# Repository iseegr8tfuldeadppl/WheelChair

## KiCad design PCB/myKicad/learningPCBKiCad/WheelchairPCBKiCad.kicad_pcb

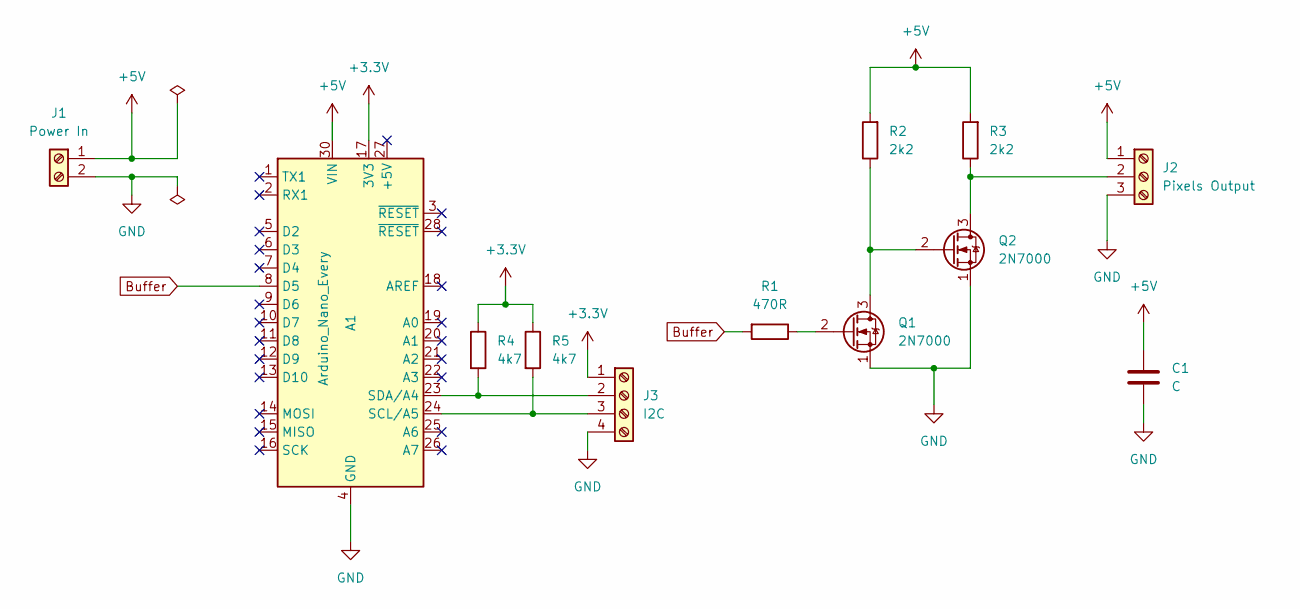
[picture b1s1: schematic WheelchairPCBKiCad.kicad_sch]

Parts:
A1: Arduino_Nano_Every; Arduino_Nano
C1: C; C_Radial_D10.0mm_H20.0mm_P5.00mm
J1: Power In; TerminalBlock_Phoenix_MKDS-3-2-5.08_1x02_P5.08mm_Horizontal
J2: Pixels Output; TerminalBlock_Phoenix_MKDS-1,5-3_1x03_P5.00mm_Horizontal
J3: I2C; TerminalBlock_Phoenix_PT-1,5-4-5.0-H_1x04_P5.00mm_Horizontal
Q1, Q2: 2N7000; TO-92L_HandSolder
R1: 470R; R_Axial_DIN0207_L6.3mm_D2.5mm_P10.16mm_Horizontal
R2, R3: 2k2; R_Axial_DIN0207_L6.3mm_D2.5mm_P10.16mm_Horizontal
R4, R5: 4k7; R_Axial_DIN0207_L6.3mm_D2.5mm_P10.16mm_Horizontal

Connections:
+3V3: A1.17 (3V3), J3.1, R4.1, R5.1
+5V: A1.30 (VIN), C1.1, J1.1, J2.1, R2.2, R3.2
Buffer: A1.8 (D5), R1.2
GND: A1.4 (GND), A1.29 (GND), C1.2, J1.2, J2.3, J3.4, Q1.1 (S), Q2.1 (S)
unnamed: A1.23 (SDA/A4), J3.2, R4.2
unnamed: A1.24 (SCL/A5), J3.3, R5.2
unnamed: Q1.2 (G), R1.1
unnamed: Q1.3 (D), Q2.2 (G), R2.1
unnamed: J2.2, Q2.3 (D), R3.1

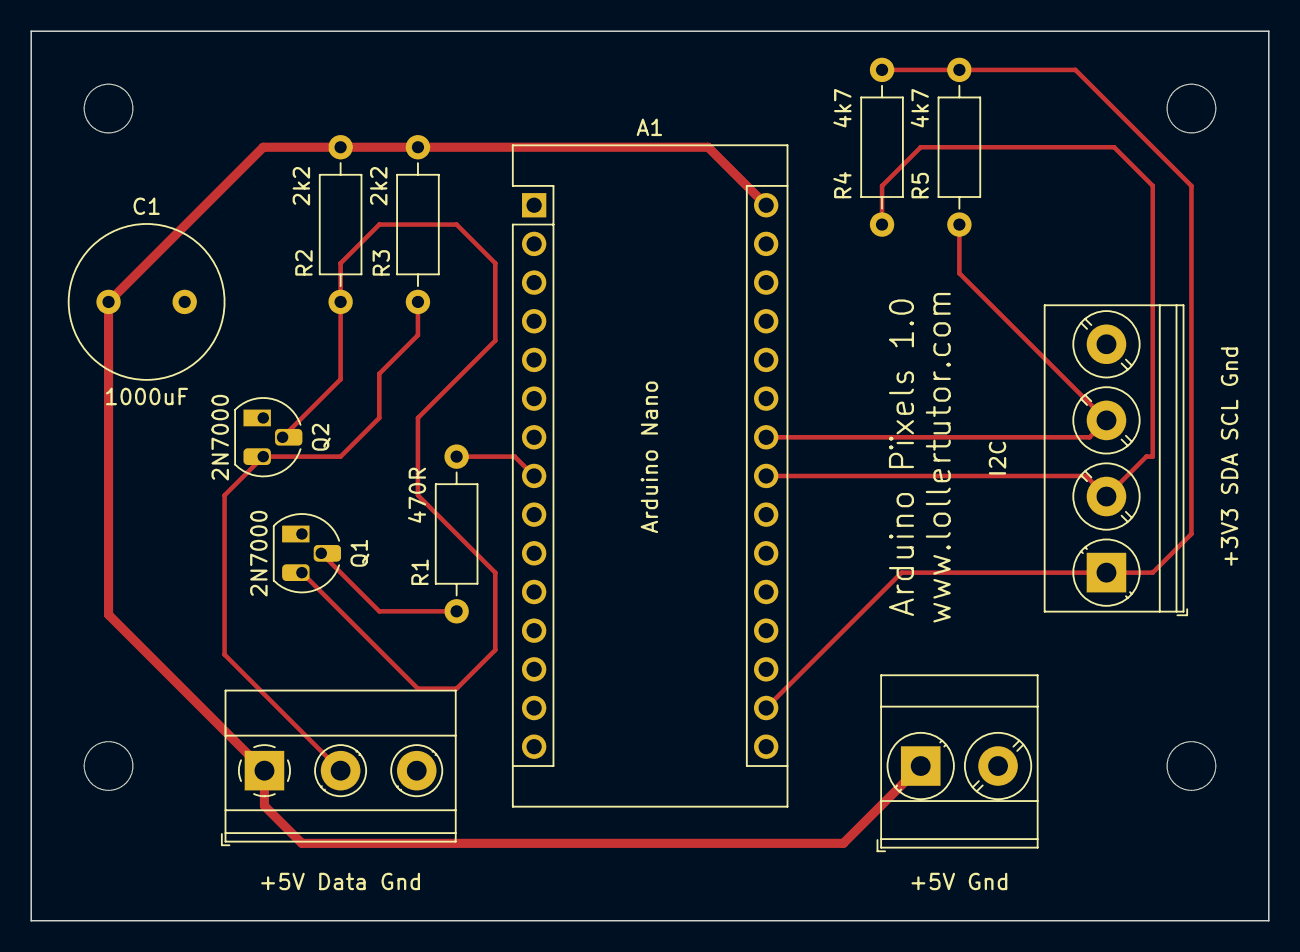
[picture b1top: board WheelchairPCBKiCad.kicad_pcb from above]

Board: 2 copper layers, 81.3 x 58.4 mm, 12 parts (0 on the bottom side), 9 nets.

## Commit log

2022-09-17 added pcb files
2023-03-12 pcb, 3d models and the like
2023-03-12 modified fritzing
2023-03-12 made a new files to send to client including optimized code and ultrasonic in schematics
2023-03-12 finished
